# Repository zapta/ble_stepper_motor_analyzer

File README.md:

# BLE STEPPER MOTOR ANALYZER

> **_NOTE:_** As for June 2023, a **productized version of a BLE Stepper Motor analyzer is available*** at https://vector3d.co.uk/product/stepper-motor-analyser/ and is firmware and software compatible with the reference design here. While we are not involved with that commercial offering, we do support such initiatives of making the technology available to the community, and will be happy to provide here technical support as much as we can.

> **_NOTE:_** As for June 24th 2023, added under the spec table a discussion regarding the **max stepper voltage** that can be used.

------

<p align="center">
  <br>
  The analyzer device of the reference design here<br>
  
</p>

<p align="center">
  The analyzer's app<br>
  
</p>

**A short video** of the app is available here https://vimeo.com/798169140

---
- [BLE STEPPER MOTOR ANALYZER](#ble-stepper-motor-analyzer)
  - [Description](#description)
  - [Design Highlights](#design-highlights)
  - [How does it work?](#how-does-it-work)
  - [Specification](#specification)
  - [Installing the device in your 3D printer](#installing-the-device-in-your-3d-printer)
  - [Using the Analyzer app.](#using-the-analyzer-app)
    - [Running the Analyzer app using a provided binary](#running-the-analyzer-app-using-a-provided-binary)
    - [Running the Analyzer app using the Python source files](#running-the-analyzer-app-using-the-python-source-files)
    - [Understanding the Analyzer app screen](#understanding-the-analyzer-app-screen)
    - [The Analyzer app buttons](#the-analyzer-app-buttons)
    - [Analyzer app command line flags](#analyzer-app-command-line-flags)
  - [Updating the firmware](#updating-the-firmware)
  - [Building your own device](#building-your-own-device)
  - [Antenna selection](#antenna-selection)
  - [Connectors](#connectors)
  - [3D Models](#3d-models)
  - [Troubleshooting connection issues](#troubleshooting-connection-issues)
  - [Hardware design files](#hardware-design-files)
  - [Firmware development](#firmware-development)
  - [Analyzer App Python development](#analyzer-app-python-development)
  - [FAQ](#faq)

---

## Description

The BLE Stepper Motor Analyzer ('the analyzer') is a low-cost, open source system that analyzes stepper motor signals and display the the data in real time on a computer screen. The system includes two parts:

1. **The Stepper Motor Probe** ('the device'). This is a small electronic board that monitors the currents through the stepper motor wires, extracts information such as steps, and speed, and transmits the data via Bluetooth BLE.

2. **The Analyzer App** ('the app'). This is a Python program that runs on a Windows, MaC OSX, or Linux PC, and displays the stepper information in real time in a graphical view.

The following block diagram shows how the device and the app related to the controller and stepper motor of an existing system such as a 3D printer. 

<p align="center">
 System Block diagram<br>
  
</p>

## Design Highlights
* The device is passive and does not interfere with the operation of the stepper motor, regardless if it is in use or turned off. Furthermore, the stepper signals are galvanically isolated from the electronics.
* Embedding the device in a 3D printer is simple. It has a small footprint, operates on 7-30 VDC, and can use a small external sticker antenna that overcomes shielding by the printer enclosure.
* The design is in the public domain (Creative Commons CC0) and can be used also commercially. Attribution and code sharing are not required.
* The device design is low cost and can be ordered fully assembled from JLCPCB or similar services.
* The device firmware can upgraded by users using a standard USB cable, no tools or adapter required.
* Each device has its fixed unique address such that multiple devices can be used and addressed independently (e.g. one for each stepper motor in your printer).
* Open BLE and Python APIs supports custom monitoring apps, such as specialized analyzers or mobile apps.

## How does it work?
The device contains two galvanic isolated current sensors that sense the currents through the two stepper coils. These values are measured 40,000 times a second and firmware on the device analyzes them and extracts information such as step count, speed, and current patterns. A Bluetooth BLE radio then transmits the data to the app which displays it in a graphical form.

 <p align="center">
 Device Block diagram<br>
  
</p>

## Specification

| Item                          | Specification                                          |
| :---------------------------- | :----------------------------------------------------- |
| Supply voltage                | 7-30 VDC                                               |
| Stepper motor voltage         | See note below                                         |
| Power consumption             | 1W max                                                 |
| Firmware update connector     | USB Type C.                                            |
| SOIC Module                   | ESP32-WROOM-32U-N4.                                    |
| Current measurement           | +/-2.5A per coil.                                      |
| PCB                           | 39mm x 43mm, two layers.                               |
| Antenna                       | 2.4Ghz external antenna IPX IPEX connector.            |
| Simultaneous connections      | 1 max.                                                 |
| Protocol                      | BLE 4.1 or higher, with Data Length Extension feature. |
| Current sensors               | CC6920BSO-5A                                           |
| Zero calibration              | Using onboard button.                                  |
| Count direction               | User selected (doesn't change motor direction).        |
| Sampling rate                 | 40Khz per channel.                                     |
| Sampling resolution           | 12bits.                                                |
| Current accuracy              | estimated at +/- 2%.                                   |
| Max step rate                 | 5K full steps/sec.                                     |
| Step resolution               | 1/100th of a full step.                                |
| Firmware programming language | C++                                                    |
| Firmware programming IDE      | VSCode, Platformio, ESPIDF framework.                  |
| Firmware debugging            | Via optional 10 pins JTAG connector.                   |
| Electronic design tool        | Kicad.                                                 |
| Mechanical design tool        | Onshape.                                               |
| Open source license           | Creative Commons CC0.                                  |

> **_NOTE:_**  The analyzer uses current sensors CC6920BSO-5A current
sensors which provides galvanic isolation between the stepper motor wires and the circuitry and input voltage of the analyzer. As a result, the stepper motor voltage is not limited, and is independent, of the supply voltage. While the sensors are specified as 3500V RMS isolation, the PCB was definitely not designed for that voltage in mind and use only 6mil clearance between the traces. Some information on the internet such as https://www.smpspowersupply.com/ipc2221pcbclearance.html suggests that this qualifies it to 50 or even 100v, but since we are not safety experts, we tested it with only 24V steppers.

## Installing the device in your 3D printer

1. Print a device carrier using a 3D printer (STL model included here) and attach the device to the carrier using two pieces of 3M VHB 1mm sticky tape or similar.
2. Attach the device carrier to the 3D printer using an additional piece of 3M VHB tape.
3. Connect the external antenna and attach the antenna to the outside of the printer.
4. Connect the motor driver and stepper motor to the two connectors as shown in the wiring diagram below. The two connectors form a path through path, such that one pair of adjacent pins are used for one coil and the other pair for the second coil.
5. Connect 7-30VDC power to the VIN connector of the device. Pay attention to polarity, though the device will not get damaged by reverse polarity. 
6. Do not connect anything to the USB connector. This connector is intended for firmware flashing only.
7. The device installation is complete. You can use your 3D printer just as you did before, regardless if the analyzer app is active or not. To monitor the stepper while your printer is turned on, use the provided analyzer app on your Windows, Mac, or Linux PC as described below. 

&nbsp;

<p align="center">
  Wiring Diagram<br>
  
</p>

## Using the Analyzer app.

### Running the Analyzer app using a provided binary
The simplest way to run the analyzer app on your computer is to look for an  executable file for your system under the 'release' directory in this repository. They also released as 'release.zip' file.

> **_NOTE:_**  The single binary files are created from the app's Python code using the Pyinstaller tool and the scripts in the python/pyinstaller directory.

### Running the Analyzer app using the Python source files
If a single app binary is not available for your system, or if you prefer to run the Python code directly, you will first need to do a few preparation to satisfy the prerequisites of the Python code.

1. Install Python on your computer. Prefer the latest stable version.
2. Clone the repository on your computer or download and extract the 'python.zip' release file.
3. Install the required python modules by running this command the 'python' directory :
   
```
pip install -r requirements.txt
```
4. Make sure that your analyzer device is powered on and start the app using the command

```
python analyzer.py
```

> **_NOTE:_**  When the device is idle, its LED blink at a rate of about 1 blink per second. When connected to the app, it blink faster about 3 blinks per second. The app can connect to a device only when it's idle as indicated by the slower blink rate.

### Understanding the Analyzer app screen

The apps screen contains the following graphs

* [A]. A rolling chart with distance in steps. Updated 50 times a second.
* [B]. A rolling chart with speed in steps/sec. Updated 50 times a second.
* [C]. A rolling chart with stepper absolute current in Amps. Updated 50 times a second. The absolute current of a stepper is sqrt(A^2 + B^2) where A and B are the momentary currents of coils A, B respectively.
* [D] A histogram of current vs speed that shows how well the driver is able to maintain the stepper current at various speeds. High coil inductance of low power voltage result in significant current level at higher speeds.
* [E] A histogram that shows the relative time spent in each speed range.
* [F] A histogram that shows the relative distance done in each speed range.
* [G] A phase (Lissajous curve) graph that shows the 'cleanliness' of the sine/cosine current signals the driver sends to the motor.
* [H] An oscilloscope graph that shows current samples from the two coils. During stepper movement in a constant speed, they should look like sine/cosine waves. 

> **_NOTE:_**  In the oscilloscope graph, a single sine or cosine cycle represents 4 stepper full steps, as shown in the graph below.

### The Analyzer app buttons
The Analyzer app contain the button listed below. 

> **_NOTE:_**  The buttons affect the app only and do not interfere with the operation of the motor.

* **Toggle Dir** - Click to change the direction of step counting.
* **Reset Data** - Click to clear the histograms and step count.
* **Time Scale X** - Click to toggle the sampling time of the signals shown in the phase graph [G] and oscilloscope graph [H] to match the movement speed. As a rule of thumb, you want to have at least one full sine/cosine wave, with higher values for slower stepper movements.
* **Pause** - Click to pause/resume the display. Useful examine interesting captured data.

> **_NOTE:_** The graphs are implemented using pyqtgraph and thus provide additional functionality that is accessible by a right mouse click on the graphs.

### Analyzer app command line flags

**--help** Prints a list with the available flags.

**--scan** The analyzer will scan for BLE devices for a few seconds, print a list of  devices it found and exit. This intended for diagnostics. The stepper motor analyzer devices have names that look like <si>STP-0C8B95F2B436</i>.

```
python analyzer.py --scan
```

**--device** Instructs the analyzer to not search on start for available devices, and instead, connect to the device with given name directly. If you set in the device a nick name using the --set-nickname flag below, you can also use that nickname as a value of the --device falg. 

```
python analyzer.py --device "STP-0C8B95F2B436"

python analyzer.py --device "X-AXIS"
```

**--set_nickname** Running the analyzer with this flags sets on the device a user friendly nickname that can be used as an alternative value for the *--device* flag. That nickname is also shown in the title of the Analyzer graphical view.

```
python analyzer.py --set_nickname "X-Axis"
```

**--max-amps** If you monitor a low current stepper motor such as a 600ma extruder motor, you can use this flag to limit the range of the current display in the Phase and Oscilloscope graphs, to zoom in on details.
```
python analyzer.py --max-amps 0.8
```

***--units*** The default units for stepper distance or rotation are full steps. You can use this flag to display other units such as mm, degrees, or extrusion mm^3. 
```
python analyzer.py --units "mm"

python analyzer.py --units "degrees"

python analyzer.py --units "mm^3"
```

**--steps_per_unit** If you are using the **--units** flag, use this flag to specify the number of full motor steps that correspond to one unit. For example, if your extruder esteps value is 540 micro steps per mm, with 16 microsteps per full step, specify the flags below:
```
python analyzer.py --units=mm --steps_per_unit 33.75
```

## Updating the firmware

To flash a firmware version follow these steps.

1. Download the release.zip file of the desired release and extract it.
2. Disconnect the power connector of the device and connect it to your computer using a USB cable.
3. Run the flash script for your Windows, Mac or Linux computer. For example:
```
flash.bat
```
 4. Verify that the the script completed with no errors and that the LED on the device is blinking at about one blink per second. The device with the new firmware is ready.

## Building your own device

1. Order assembled boards (recommended), or just order bare PCBs and assemble the components yourself. Production files for JLCPCB PCB, including for the SMT service are included in this repository.
2. Connect the device to a computer via a USB cable and notice that one LED turn on solid to indicate 3.3V power.
3. Flash the device with firmware as explained above.
4. Calibrate the current sensors for zero level by long pressing the switch until the second LED will blink 3 times to indicate that the calibration values were saved in the non volatile memory.
5. Connect an antenna, run an analyzer program as explain above and that you see some signals from the device. The LED on the device will blink faster to indicate an active connection.
6. The device is now ready for installation in the 3D printer or for shipping to your customers.

* **Schematic**: https://github.com/zapta/ble_stepper_motor_analyzer/blob/main/kicad/stepper_monitor.pdf
* **JLCPCB production files**: https://github.com/zapta/ble_stepper_motor_analyzer/tree/main/kicad/JLCPCB

> **_NOTE:_**  Resistor R16 acts as a jumper and allows to disconnect the 3.3V supply from the rest of the electronics. This is useful when diagnosing power issues.

## Antenna selection

The external antenna should  satisfy these requirements:
* Specified for the Bluetooth band of 2.4GHZ.
* Having a connector that match the ESP32 WROOM module. The connector has several names including IPEX, U.FL, or MHF1, but it's easier to distinguish it by its wider body.

<p align="center">
  Inexpensive Aliexpress sticker antennas.<br>
  
</p>

## Connectors

* **Stepper Motor Connectors** - KF2510 connector 2.54mm pitch, female, 4 wires.
* **Vin connector** - Dupont 2.54mm pitch, female, 2 wires. 

## 3D Models

3D Models of the carrier and a cover for shipping are available at https://github.com/zapta/ble_stepper_motor_analyzer/tree/main/3D

## Troubleshooting connection issues

The analyzer requires on the PC side support for Bluetooth BLE 4.1 or higher with support for the Data Length Extension feature. It is expected that most computer come with a built in adapters that support
this standard, but we also observed a very low cost BeeLink mini computer that came with an old internal Bluetooth adapter that doesn't support this standard.

The workaround in this case is to **disable the internal Bluetooth adapter** and use an **external USB Bluetooth adapter** that has an external antenna for better range. For example we had good result with this adapter that as of 2023 cost about $15 https://www.amazon.com/gp/product/B09KGVFX1K, which is based on the RTL876B chip.

> **_NOTE:_**  Installing a RTL876B based adapter on Ubuntu requires a minor tweak of the firmware file names as explained at https://fosspost.org/fix-bluetooth-rtl8761b-problem-on-linux-ubuntu-22-04/. Also, 

The symptoms of a PC bluetooth adapter that doesn't support the required protocol are that the device shows up when running *analyzer --scan* but when running the analyzer without the *--scan* flag, it fails to connect to the device.  For the more technical readers, a discussion on this topic is available here https://github.com/hbldh/bleak/issues/1227#issuecomment-1435708347

## Hardware design files

The Kicad source files and the generated JLCPCB production files are available under the *kicad* directory of this repository. As of Mar 2023, we are using Kicad 7.0, and the built in plugins **Fabrication Toolkit** and **Interactive Html Bom**.

## Firmware development

This list below outlines the steps to set up your own firmware development environment.

1. Install Visual Studio Code (VSC).
2. In Visual Studio Code, enable the <i>platformio</i> extension.
3. Download or clone this git repository on your computer.
4. In VSC, select <i>File | Open Folder</i> and select the 'platformio' directory.
5. Connect a device to your computer using a USB cable. This will create a serial port on your computer.
6. Click on the platformio <i>Upload</i> icon at the bottom of the screen (right arrow icon) and platformio will automatically install all the dependencies, build the project, and upload it to your device via the serial port.  
7. For more information on how to use platformio, check http://platformio.org.

> **_NOTE:_**  For optional hardware debugging (breakpoints, single step, etc), you will need an Espressif ESP-Prog Development Board, and to solder on your device a 10 pins JTAG connector.

> **_NOTE:_** It's OK to connect a stepper motor to the device while you develope code since the stepper signals are galvanically isolated from the USB interface and from your computer.

> **_NOTE:_** It is recommended to not connect VIN and the USB connectors at the same time to avoid ground loop, in case both the Vin power supply and your computer are grounded independently.

## Analyzer App Python development

The Analyzer's Python app is stored in the 'python/analyzer' directory and uses a library at python/common. The app is based on Bleak (BLE client) PyQtGraph (a graphing library) and uses asyncio for non blocking background operation. The list of requires python modules is in requirements.txt and they can be installed using the command

```
pip install -r requirements.txt
```

## FAQ

**Q**: This is an exciting project, can I help?

A: Of course, contribution of code, documentation, test programs or ideas are welcome.

---

**Q**: I want to monitor multiple motors in my 3D printer. Is it possible?

**A**: Of course. Simply install a device for each stepper motor you want to monitor. 

---

**Q**: I am using multiple devices, how can I select which one I connect to? 

**A**: Each device has a fixed unique name such STP-0C8B95F2B436. When you run the analyzer app, it will allow you to select a device, if more than one are available, or you can use the --device flag to force a specific device.

---

**Q**: How far can my computer be away from my 3D printer? 

**A**: Bluetooth BLE radio communication is intended for short distances of a few yards. If the radio link will not be reliable, the analyzer program will detect data gaps and will report it in its console log.

---

**Q**: This system can be a great idea for a Crowd Compute campaign. Can I do that? 

**A**: Of course. The design is in public domain and commercial usages are encouraged. Attribution and sharing of modification you make are not required. 

---

**Q**: Do you sell boards? 

**A**: We may produce a limited numbers of boards from time to time, but we also believe that others can do a better job job of mass producing and making it available to the community.

---

**Q**: Can the external antenna be eliminated to simplify installation and reduce cost? 

**A**: Yes. We believe that the ESP module ESP32-WROOM-32D-N4 which uses an internal antenna should be a drop-in replacement though we did not have the chance yet to test it.

---

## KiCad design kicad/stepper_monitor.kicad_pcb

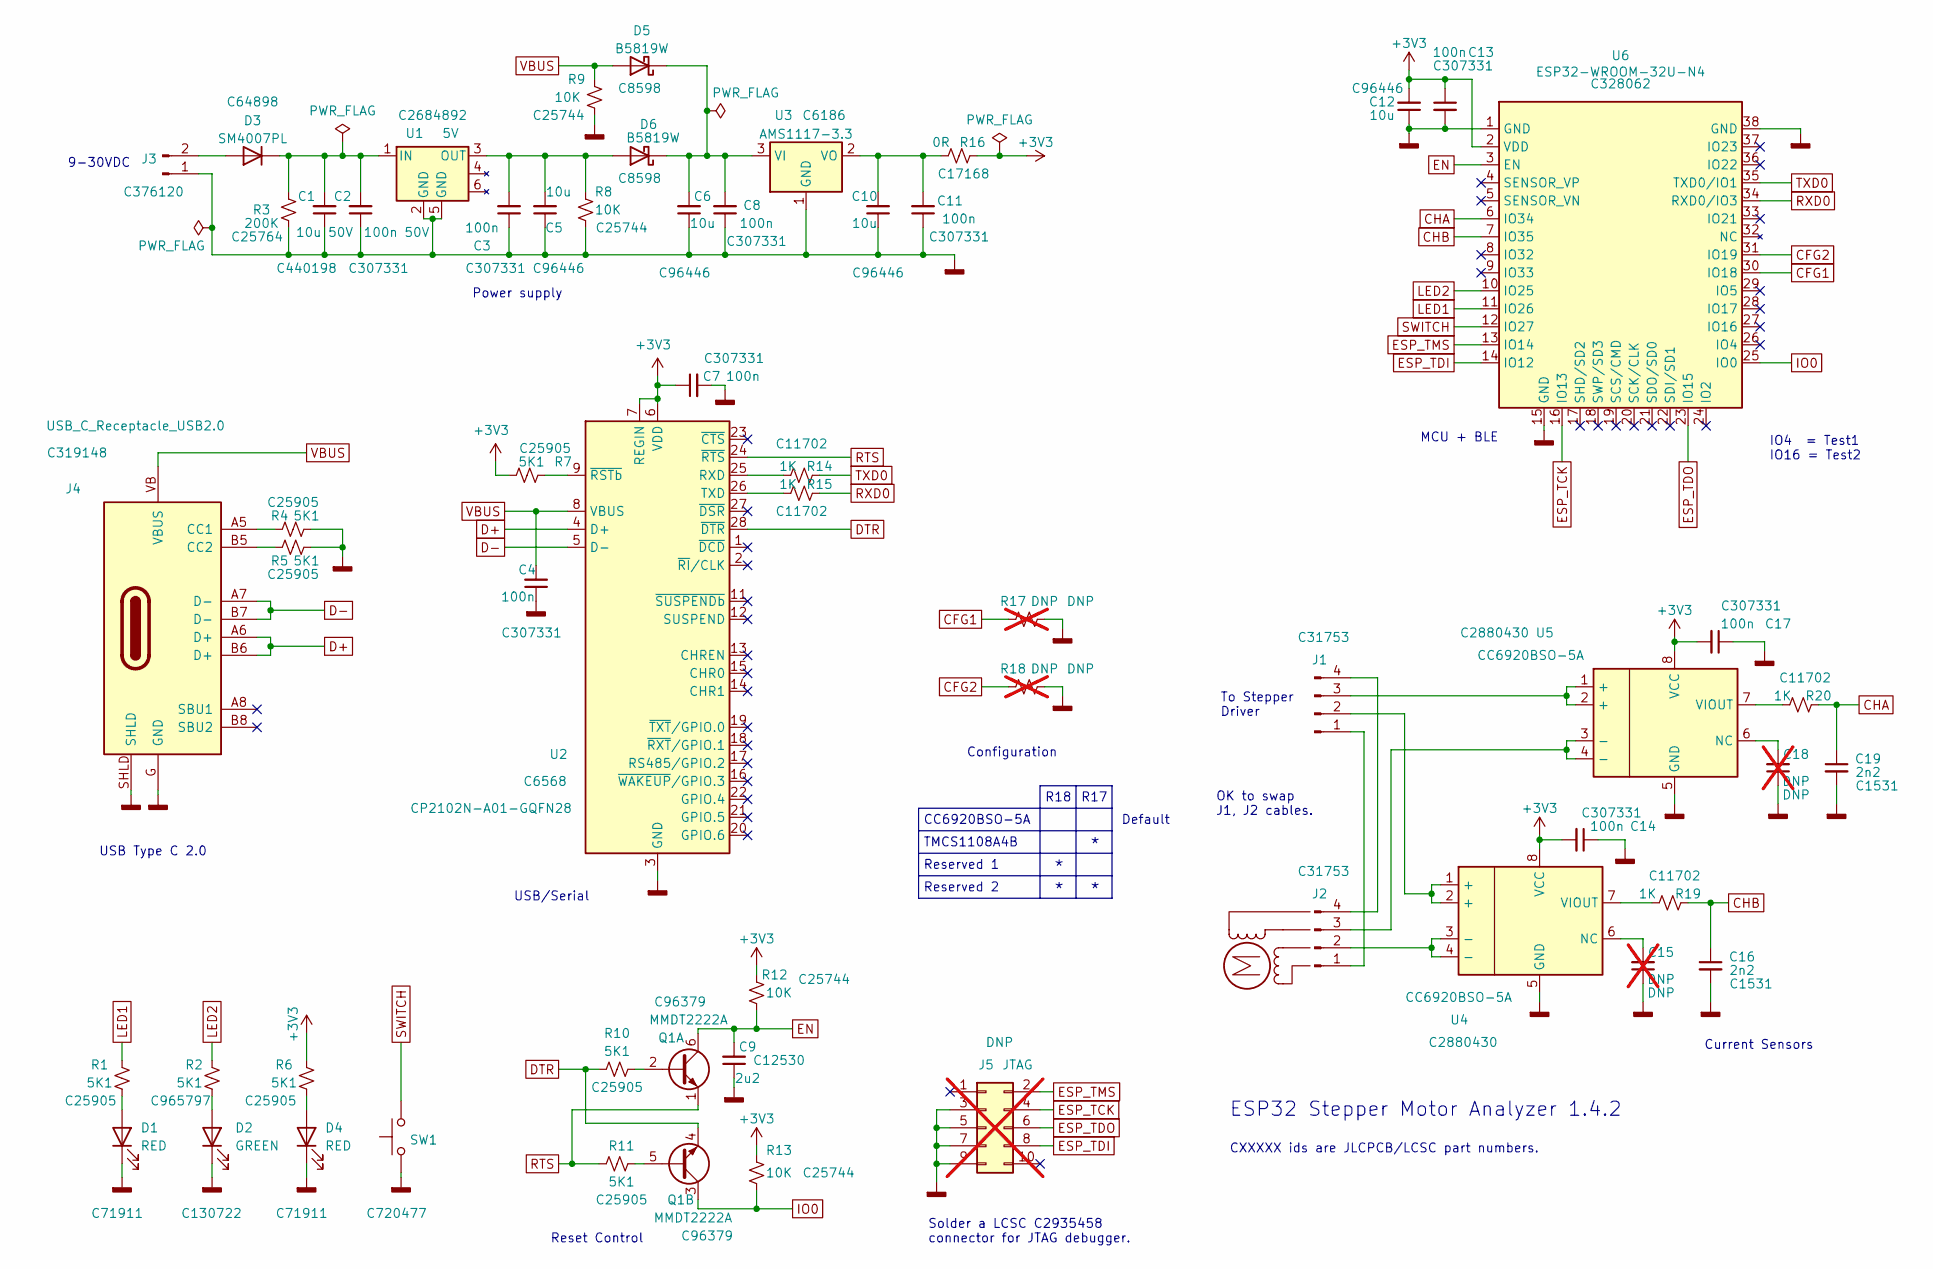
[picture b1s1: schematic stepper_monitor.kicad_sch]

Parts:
C1: 10u 50V; C_0805_2012Metric; LCSC C440198
C2: 100n 50V; C_0402_1005Metric; LCSC C307331
C3, C4, C7, C8, C11, C13, C14, C17: 100n; C_0402_1005Metric; LCSC C307331
C5, C6, C10, C12: 10u; C_0603_1608Metric; LCSC C96446
C9: 2u2; C_0402_1005Metric; LCSC C12530
C15, C18: DNP; C_0402_1005Metric; LCSC DNP; not fitted
C16, C19: 2n2; C_0402_1005Metric; LCSC C1531
D1, D4: RED; LED_0402_1005Metric_Pad0.77x0.64mm_HandSolder; LCSC C71911
D2: GREEN; LED_0402_1005Metric_Pad0.77x0.64mm_HandSolder; LCSC C130722
D3: SM4007PL; D2_SOD-123; LCSC C64898
D5, D6: B5819W; D_SOD-123; LCSC C8598
J1, J2: Conn_01x04_Pin; connector_4pins_horizontal; LCSC C31753
J3: Conn_01x02_Pin; PinHeader_1x02_P2.54mm_Horizontal_JLCPCB; LCSC C376120
J4: USB_C_Receptacle_USB2.0; USB_C_Receptacle_XKB_U262-16XN-4BVC11; LCSC C319148
J5: JTAG; PinHeader_2x05_P1.27mm_Vertical_SMD; LCSC DNP; not fitted
M1: Motor-simple_stepper_motor_analyzer; Empty
Q1: MMDT2222A; SOT-363_SC-70-6; LCSC C96379
R1, R4, R5, R6, R7, R10, R11: 5K1; R_0402_1005Metric; LCSC C25905
R2: 5K1; R_0402_1005Metric; LCSC C965797
R3: 200K; R_0402_1005Metric; LCSC C25764
R8, R9, R12, R13: 10K; R_0402_1005Metric; LCSC C25744
R14, R15, R19, R20: 1K; R_0402_1005Metric; LCSC C11702
R16: 0R; R_0402_1005Metric; LCSC C17168
R17, R18: DNP; R_0402_1005Metric; LCSC DNP; not fitted
SW1: SW_Push; SW_Push_SPST_NO_Alps_SKRK; LCSC C720477
U1: 5V; Converter_DCDC; LCSC C2684892
U2: CP2102N-A01-GQFN28; QFN-28-1EP_5x5mm_P0.5mm_EP3.35x3.35mm; LCSC C6568
U3: AMS1117-3.3; SOT-223-3_TabPin2; LCSC C6186
U4, U5: CC6920BSO-5A; SOIC-8_3.9x4.9mm_P1.27mm; LCSC C2880430
U6: ESP32-WROOM-32U-N4; ESP32-WROOM-32U; LCSC C328062

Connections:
+3V3: C7.1, C12.2, C13.1, C14.2, C17.2, R6.2, R7.2, R12.2, R13.2, R16.1, U2.6 (VDD), U2.7 (REGIN), U4.8 (VCC), U5.8 (VCC), U6.2 (VDD)
CFG1: R17.1, U6.30 (IO18)
CFG2: R18.1, U6.31 (IO19)
CHA: C19.1, R20.1, U6.6 (IO34)
CHB: C16.1, R19.1, U6.7 (IO35)
D+: J4.A6 (D+), J4.B6 (D+), U2.4 (D+)
D-: J4.A7 (D-), J4.B7 (D-), U2.5 (D-)
DTR: Q1.4 (E2), R10.1, U2.28 (~DTR)
EN: C9.2, Q1.6 (C1), R12.1, U6.3 (EN)
ESP_TCK: J5.4, U6.16 (IO13)
ESP_TDI: J5.8, U6.14 (IO12)
ESP_TDO: J5.6, U6.23 (IO15)
ESP_TMS: J5.2, U6.13 (IO14)
GNDD: C1.1, C2.1, C3.1, C4.1, C5.1, C6.1, C7.2, C8.1, C9.1, C10.1, C11.1, C12.1, C13.2, C14.1, C15.1, C16.2, C17.1, C18.1, C19.2, D1.1 (K), D2.1 (K), D4.1 (K), J3.1, J4.G (GND), J4.SHLD, J5.3, J5.5, J5.7, J5.9, R3.2, R4.1, R5.1, R8.1, R9.1, R17.2, R18.2, SW1.1, U1.2 (GND), U1.5 (GND), U2.3 (GND), U2.29 (GND), U3.1 (GND), U4.5 (GND), U5.5 (GND), U6.1 (GND), U6.15 (GND), U6.38 (GND), U6.39 (GND)
IO0: Q1.3 (C2), R13.1, U6.25 (IO0)
LED1: R1.2, U6.11 (IO26)
LED2: R2.2, U6.10 (IO25)
unnamed: C1.2, C2.2, D3.1 (K), R3.1, U1.1 (IN)
unnamed: C6.2, C8.2, D5.1 (K), D6.1 (K), U3.3 (VI)
unnamed: D1.2 (A), R1.1
unnamed: D2.2 (A), R2.1
unnamed: D3.2 (A), J3.2
unnamed: D4.2 (A), R6.1
unnamed: C3.2, C5.2, D6.2 (A), R8.2, U1.3 (OUT)
unnamed: J1.1, J2.1
unnamed: J1.2, U4.1 (+), U4.2 (+)
unnamed: J1.3, U5.1 (+), U5.2 (+)
unnamed: J1.4, J2.4
unnamed: J2.2, U4.3 (-), U4.4 (-)
unnamed: J2.3, U5.3 (-), U5.4 (-)
unnamed: J4.A5 (CC1), R4.2
unnamed: J4.B5 (CC2), R5.2
unnamed: Q1.2 (B1), R10.2
unnamed: Q1.5 (B2), R11.1
unnamed: R14.2, U2.25 (RXD)
unnamed: R15.2, U2.26 (TXD)
unnamed: R7.1, U2.9 (~RSTb)
unnamed: C10.2, C11.2, R16.2, U3.2 (VO)
unnamed: C15.2, U4.6 (NC)
unnamed: R19.2, U4.7 (VIOUT)
unnamed: C18.2, U5.6 (NC)
unnamed: R20.2, U5.7 (VIOUT)
RTS: Q1.1 (E1), R11.2, U2.24 (~RTS)
RXD0: R15.1, U6.34 (RXD0/IO3)
SWITCH: SW1.2, U6.12 (IO27)
TXD0: R14.1, U6.35 (TXD0/IO1)
VBUS: C4.2, D5.2 (A), J4.VB (VBUS), R9.2, U2.8 (VBUS)

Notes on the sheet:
Solder a LCSC C2935458 connector for JTAG debugger.
TMCS1108A4B
Current Sensors
Reserved 2
IO4 = Test1 IO16 = Test2
CXXXXX ids are JLCPCB/LCSC part numbers.
Reserved 1
To Stepper Driver
Configuration
USB Type C 2.0
9-30VDC
USB/Serial
OK to swap J1, J2 cables.
Reset Control
Default
R17
CC6920BSO-5A
R18
MCU + BLE
Power supply
ESP32 Stepper Motor Analyzer 1.4.2

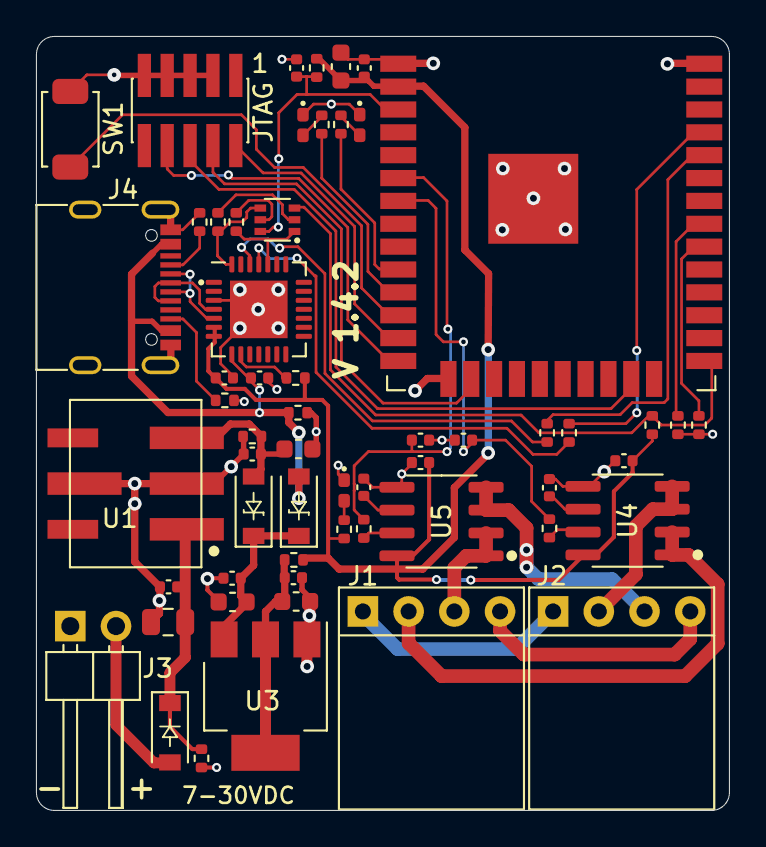
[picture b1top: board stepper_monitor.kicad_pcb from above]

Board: 2 copper layers, 38.5 x 43.0 mm, 58 parts (0 on the bottom side), 47 nets.

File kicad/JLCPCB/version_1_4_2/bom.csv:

Designator,Footprint,Quantity,Value,LCSC Part #
C1,0805,1,10u 50V,C440198
"C10, C12, C5, C6",0603,4,10u,C96446
"C11, C13, C14, C17, C3, C4, C7, C8",0402,8,100n,C307331
"C15, C18, R17, R18",0402,4,DNP,DNP
"C16, C19",0402,2,2n2,C1531
C2,0402,1,100n 50V,C307331
C9,0402,1,2u2,C12530
"D1, D4",0402,2,RED,C71911
D2,0402,1,GREEN,C130722
D3,D2_SOD-123,1,SM4007PL,C64898
"D5, D6",D_SOD-123,2,B5819W ,C8598
"J1, J2",connector_4pins_horizontal,2,Conn_01x04_Pin,C31753
J3,PinHeader_1x02_P2.54mm_Horizontal_JLCPCB,1,Conn_01x02_Pin,C376120
J4,USB_C_Receptacle_XKB_U262-16XN-4BVC11,1,USB_C_Receptacle_USB2.0,C319148
J5,PinHeader_2x05_P1.27mm_Vertical_SMD,1,JTAG,DNP
Q1,SOT-363_SC-70-6,1,MMDT2222A,C96379
"R1, R10, R11, R2, R4, R5, R6, R7",0402,8,5K1,C25905
"R12, R13, R8, R9",0402,4,10K,C25744
"R14, R15, R19, R20",0402,4,1K,C11702
R16,0402,1,0R,C17168
R3,0402,1,200K,C25764
SW1,SW_Push_SPST_NO_Alps_SKRK,1,SW_Push,C720477
U1,Converter_DCDC,1,5V,C2684892
U2,QFN-28-1EP_5x5mm_P0.5mm_EP3.35x3.35mm,1,CP2102N-A01-GQFN28,C6568
U3,SOT-223-3_TabPin2,1,AMS1117-3.3,C6186
"U4, U5",SOIC-8_3.9x4.9mm_P1.27mm,2,CC6920BSO-5A,C2880430
U6,ESP32-WROOM-32U,1,ESP32-WROOM-32U-N4,"C328062
"

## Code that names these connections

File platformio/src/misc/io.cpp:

#include "io.h"

#include "driver/gpio.h"

namespace io {

// Digital outputs.
OutputPin LED1(GPIO_NUM_26, 1);
OutputPin LED2(GPIO_NUM_25, 1);

// Digital inputs.
static InputPin SWITCH1(GPIO_NUM_27, GPIO_PULLUP_ONLY);
Button BUTTON1(SWITCH1);

static InputPin CFG1(GPIO_NUM_18, GPIO_PULLUP_ONLY);
static InputPin CFG2(GPIO_NUM_19, GPIO_PULLUP_ONLY);

uint8_t read_hardware_config() {
  return (CFG1.is_high() ? 0 : 0x01) | (CFG2.is_high() ? 0 : 0x02);
}

}  // namespace io

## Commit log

2022-08-31 Initial esp32 project.
2022-09-01 Regenerated the ESP32 startup project.
2022-09-02 Moved main to .cpp
2022-09-02 Experimenting.
2022-09-04 Works with ESP32 mini
2022-09-04 Initial esp32 kicad.
2022-09-06 Updated to Kicad 6
2022-09-08 Work in progress.
2022-09-10 Updated the schematic: Fixed the power selection circuit.
2022-09-10 Cleaned up a few footprints.
2022-09-11 Initial placement and routing. Needs TLC.
2022-09-11 Fixed non available JLCPCB parts.
2022-09-11 Topologically correct routing. Needs TLC.
2022-09-11 Cleaned up the layout.
2022-09-11 Connected USB shield to ground.
2022-09-13 Cleaned up the PCB layout.
2022-09-13 Minor PCB layout tweaks.
2022-09-15 Added basic IO.
2022-09-15 Minor project config tweak.
2022-09-15 Added time utils.
2022-09-15 Added i/o and button logic.
2022-09-15 Added i/o logic.
2022-09-19 Added skeleton ble files.
2022-09-19 Enabled bt in sdkconfig
2022-12-28 Work in progress
2022-12-28 Added comment.
2023-01-01 adc works, 20k 1 chan
2023-01-01 Sampling two channles (6, 7)
2023-01-01 Updated analog input pins.
2023-01-03 Working version.
2023-01-03 Cleanup
2023-01-04 Cleanup. Working.
2023-01-04 Cleanup.
2023-01-05 Added analyzer. Working.
2023-01-05 Added test point.
2023-01-05 Adjusted ADC offset.
2023-01-12 Added ADC capacitors.
2023-01-14 Stable ADC sampling.
2023-01-14 Added eeprom api.
2023-01-14 Added settings controls.
2023-01-14 Clenaup
2023-01-14 Added LEDs blinks.
2023-01-14 Added led blinks (leftover files)
2023-01-14 Converted the project from CRLF to LF.
2023-01-15 Tweaks. Increased flash partition to 1.5M.
2023-01-15 Added source paths for intellisense.
2023-01-15 Deleted auto generated files.
2023-01-15 Ignoring two auto generated files.
2023-01-15 Add source path.
2023-01-15 Disable ble setup.
2023-01-16 added ble2 (table driven).
2023-01-17 BLE work in progress. Device name now includes device address.
2023-01-18 Cleaned up ble service
2023-01-18 Added connection detection.
2023-01-19 Added notification control.
2023-01-21 Added static info charc.
2023-01-21 Copied python directory from nrf project.
2023-01-21 Deleted an orphan arduino file
2023-01-22 More cleanup.
2023-01-22 Implemented two more read handlers.
2023-01-23 Added notifications + cleanup
2023-01-23 Added connection blinking control + cleanup.
2023-01-23 More cleanups
2023-01-23 Added command end point, for now as a read only.
2023-01-24 Added command end point.
2023-01-24 First version that works with the client.
2023-01-24 Added hardware config and .clang-format.
2023-01-24 Code cleanup.
2023-01-24 Renamed ble_service to ble_host
2023-01-25 Tweaked clang-format
2023-01-25 Removed unused unit test.
2023-01-25 Cleaned up ble attribute declarations (using macros).
2023-01-25 Tested the hardware config inputs.
2023-01-25 Prepared for a BLE Host mutex.
2023-01-25 Added BLE host mutex.
2023-01-25 Added pin TEST2.
2023-01-25 Processed TODOs.
2023-01-25 Added a TODO
2023-01-26 Updated capacitor value from 4u7 to 2u2.
2023-01-26 Minor tweaks
2023-01-26 Change adc filter caps from 4.7n to 2.2n
2023-01-26 Calibrated current sensors.
2023-01-26 Added a comment.
2023-01-26 Updated led and npn to available parts.
2023-01-27 Updated PCB for external antenna + cleanups.
2023-01-27 Fixed schematic footprints.
2023-01-28 Cleaned up library reference
2023-01-28 Added JLCPCB production files.
2023-01-28 Added esptool
2023-01-28 Changed yellow LED to green.
2023-01-28 Simplified esptool command
2023-01-28 Minor cleanup
2023-01-28 Updated TODOs
2023-01-28 Added parsing of device name and merged the scanner into the analyzer.
2023-01-28 Added analyzer.exe
2023-01-28 Minor tweaks.
2023-01-29 Moved the analyzer's src directory.
2023-01-29 Updated windows flasher.
2023-01-29 Added automatic selection of devices.
2023-01-29 Updated analyzer.exe
2023-01-29 Added scanner test program. Increased esptool speed.
2023-01-29 Added nrf snifer for wireshak.
2023-02-08 Changed solder jumper to 0 ohms resistor.
2023-02-08 Deleted obsolete Kicad files.
2023-02-09 Added 3D models
2023-02-10 Added printout of efuses.
2023-02-10 Tweaked a log message.
2023-02-11 Simplify the power supply using a diode based design.
2023-02-12 Simplified platformio.ini. Removed debug and release build targets.
2023-02-12 Simplified the directory structure of the app's python code.
2023-02-12 Renamed directory 'kicad' to 'hardware'.
2023-02-12 Renamed directory 'platformio' to 'firmware'.
2023-02-12 Deleted the nordic nrf sniffer.
2023-02-12 Cleaned up docs directory.
2023-02-12 Generated JLCPCB produciton files.
2023-02-12 Updated README.
2023-02-12 Doc work in progress.
2023-02-12 Docs.
2023-02-12 Doc in progress.
2023-02-13 Added table of content
2023-02-13 Updated doc. Created pyinstaller version.
2023-02-15 Changed LCSC part number of green LED
2023-02-16 Renamed jj5 to j5. Increased version to 1.4.2. This is one commit past order of 1.4.1 from JLCPCB.
2023-02-16 Removed references to Windows specific dependencies.
2023-02-16 Added a test for connection cleanup.
2023-02-16 Added a connection test with at exit cleanup.
2023-02-16 Updated python test programs.
2023-02-17 Made connection cleanup at exit conditional.
2023-02-17 Updated .gitignore
2023-02-17 Added write command test.
2023-02-17 Renamed test
2023-02-17 Added atexit connection cleanup
2023-02-18 Changed chrc from write to write-nr.
2023-02-18 Added block reading test.
2023-02-18 minor tweak
2023-02-18 Updated TODO.
2023-02-19 Added bluetooth core specification 4.2 (pdf)
2023-02-20 Restructured app directories
2023-02-20 Renamed analyzer.py to analyzer_main.py
2023-02-21 Cleaned up python packages.
2023-02-21 Work in progress on connection management.
2023-02-22 Addeed device side disconnection.
2023-02-22 Auto formatted connections.py
2023-02-22 Added TODO
2023-02-22 Generated a good linux binary.
2023-02-22 Added flasher for linux
2023-02-22 Rebuilt the app for windows
2023-02-22 Rebuilt firmware
2023-02-23 Minor cleanup.
2023-02-25 Upgraded to espidf 5.
2023-02-25 Added .gitattributes file
2023-02-25 Upgraded kicad to 7.0 (design version incremented to 1.4.2)
2023-02-25 Added ibom
2023-02-25 Updated TODO.txt
2023-02-25 Changed platformio.ini comments from ; to #.
2023-02-25 Added throughput test
2023-02-25 Added notes file.
2023-02-25 Updated TODO and throughput test.
2023-02-26 sdkconfig tweaks. Increase cpu speed 160 -> 240mhz
2023-02-26 Updated firmware bin files
2023-02-26 Renamed directories to kicad, platformio, and python. No other change.
2023-02-27 Cleanup graph update tasks.
2023-02-27 Cleanup graph update tasks
2023-02-27 Cleaned up the analyzer's periodic tasks.
2023-02-27 Updated TODO
2023-02-27 Regenerated firmware binaries
2023-02-27 Regenerated analyzer's windows binary.
2023-02-28 Fixed nvs write crash. Updated firmware binary files.
2023-02-28 Added scan sort
2023-02-28 Added list of available linux chip drivers
2023-02-28 Updated to full linux bt drivers (firmware files)
2023-02-28 Fixed the device sorting.
2023-02-28 Regenerated firmware binaries.
2023-03-01 Generated analyzer binary for windows
2023-03-01 Renamed 'linux' to 'ubuntu'
2023-03-01 Regenerated ubuntu analyzer.
2023-03-02 Updated ubuntu flasher.
2023-03-05 Skeleton script for mac.
2023-03-05 Test
2023-03-05 Generated mac binary.
2023-03-06 Tweaked Analyzer for Mac.
2023-03-06 Changed device lookup from by address to by name.
2023-03-06 Regenerated mac analyzer binary
2023-03-08 Created windows binary.
2023-03-08 Generated a binary for ubuntu.
2023-03-19 Added paused states queue.
2023-03-19 Changed the tasks to not block the timer handler.
2023-03-19 Updated windows binary.
2023-03-19 Changed build_on_windows from a bash script to a batch script.
2023-03-19 Added formatter config to python project
2023-03-19 Regenerated the mac binary file.
2023-03-19 Formatted the python files. No logic change.
2023-03-19 Tweaked the base line of the histograms.
2023-03-19 Rebuilt the windows binary.
2023-03-20 Added 3D models, regenerated production files (new plugin version). No electrical changes.
2023-03-20 Versioned the espressif platform.
2023-03-21 Added device version string.
2023-03-21 Cleaned up the app version string.
2023-03-21 Added 3d model for the switch.
2023-03-21 Fixed a typo.
2023-03-21 Rebuilt windows binary.
2023-03-21 Added 3D model for tactile switch.
2023-03-21 Regenerated firmware and windows binaries.
2023-03-21 Minor python app tweak. Also regenerated windows binary.
2023-03-21 Regenerated mac binary.
2023-03-21 Rebuilt firmware binary in a clean client.
2023-03-21 Generated analyzer binary for ubuntu.
2023-03-22 Updated documentation
2023-03-22 Renamed flag --device-nick-name to --device-nickname.
2023-03-22 Regenerted the windows binary.
2023-03-22 Updated the doc with external BT adapter info.
2023-03-22 Minor doc fix.
2023-03-22 Minor doc tweak.
2023-03-22 Minor doc update.
2023-03-24 Upgraded kicad 7.0.0 -> 7.0.1
2023-04-04 Added nordic sniffer
2023-04-05 Added support for device side nickname.
2023-04-05 Formmated scan output by columns
2023-04-06 Command set-nickname now uses a write with response.
2023-04-06 Removed the post set-nickname delay. Not needed since the command is now with response.
2023-04-06 Added to the scan printout of rssi
2023-04-06 Added a TODO item.
2023-04-06 Minor typo fix.
2023-04-06 Added a test program.
2023-04-06 Adapted test to use device name instead of address.
2023-04-07 Tweaked the wdt test.
2023-04-08 Fixed the atexit disconnect on widnows. Disabled WDT heatbeat.
2023-04-08 Forcing exit(0) as a workaround for Mac OSX zsh printing error messages on exit.
2023-04-09 Tweaked the atexit handling.
2023-04-09 Minor firmware cleanup around updating the ble settings.
2023-04-09 Updated the docs.
2023-04-09 Rebuilt binary for windows.
2023-04-09 Created ubuntu binary
2023-04-09 Generated firmware binaries.
2023-04-09 Rebuilt firmware binaries.
2023-06-07 Added text and link for Vector 3D's product.
2023-06-07 Simplified the Vector 3D text.
2023-06-07 Tweaked the text.
2023-06-23 fix links
2023-06-24 Added a discussion of max stepper voltage that can be used.
2023-07-11 Fixe the part number of the USB serial IC to CP2102 (was CP2102N). The LCSC part number C6568 was correct and was not changed..
2023-10-08 Updated windows build file for latest python and pyqtgraph

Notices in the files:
README.md:
A**: Of course. The design is in public domain and commercial usages are encouraged. Attribution and sharing of modification you make are not required.
